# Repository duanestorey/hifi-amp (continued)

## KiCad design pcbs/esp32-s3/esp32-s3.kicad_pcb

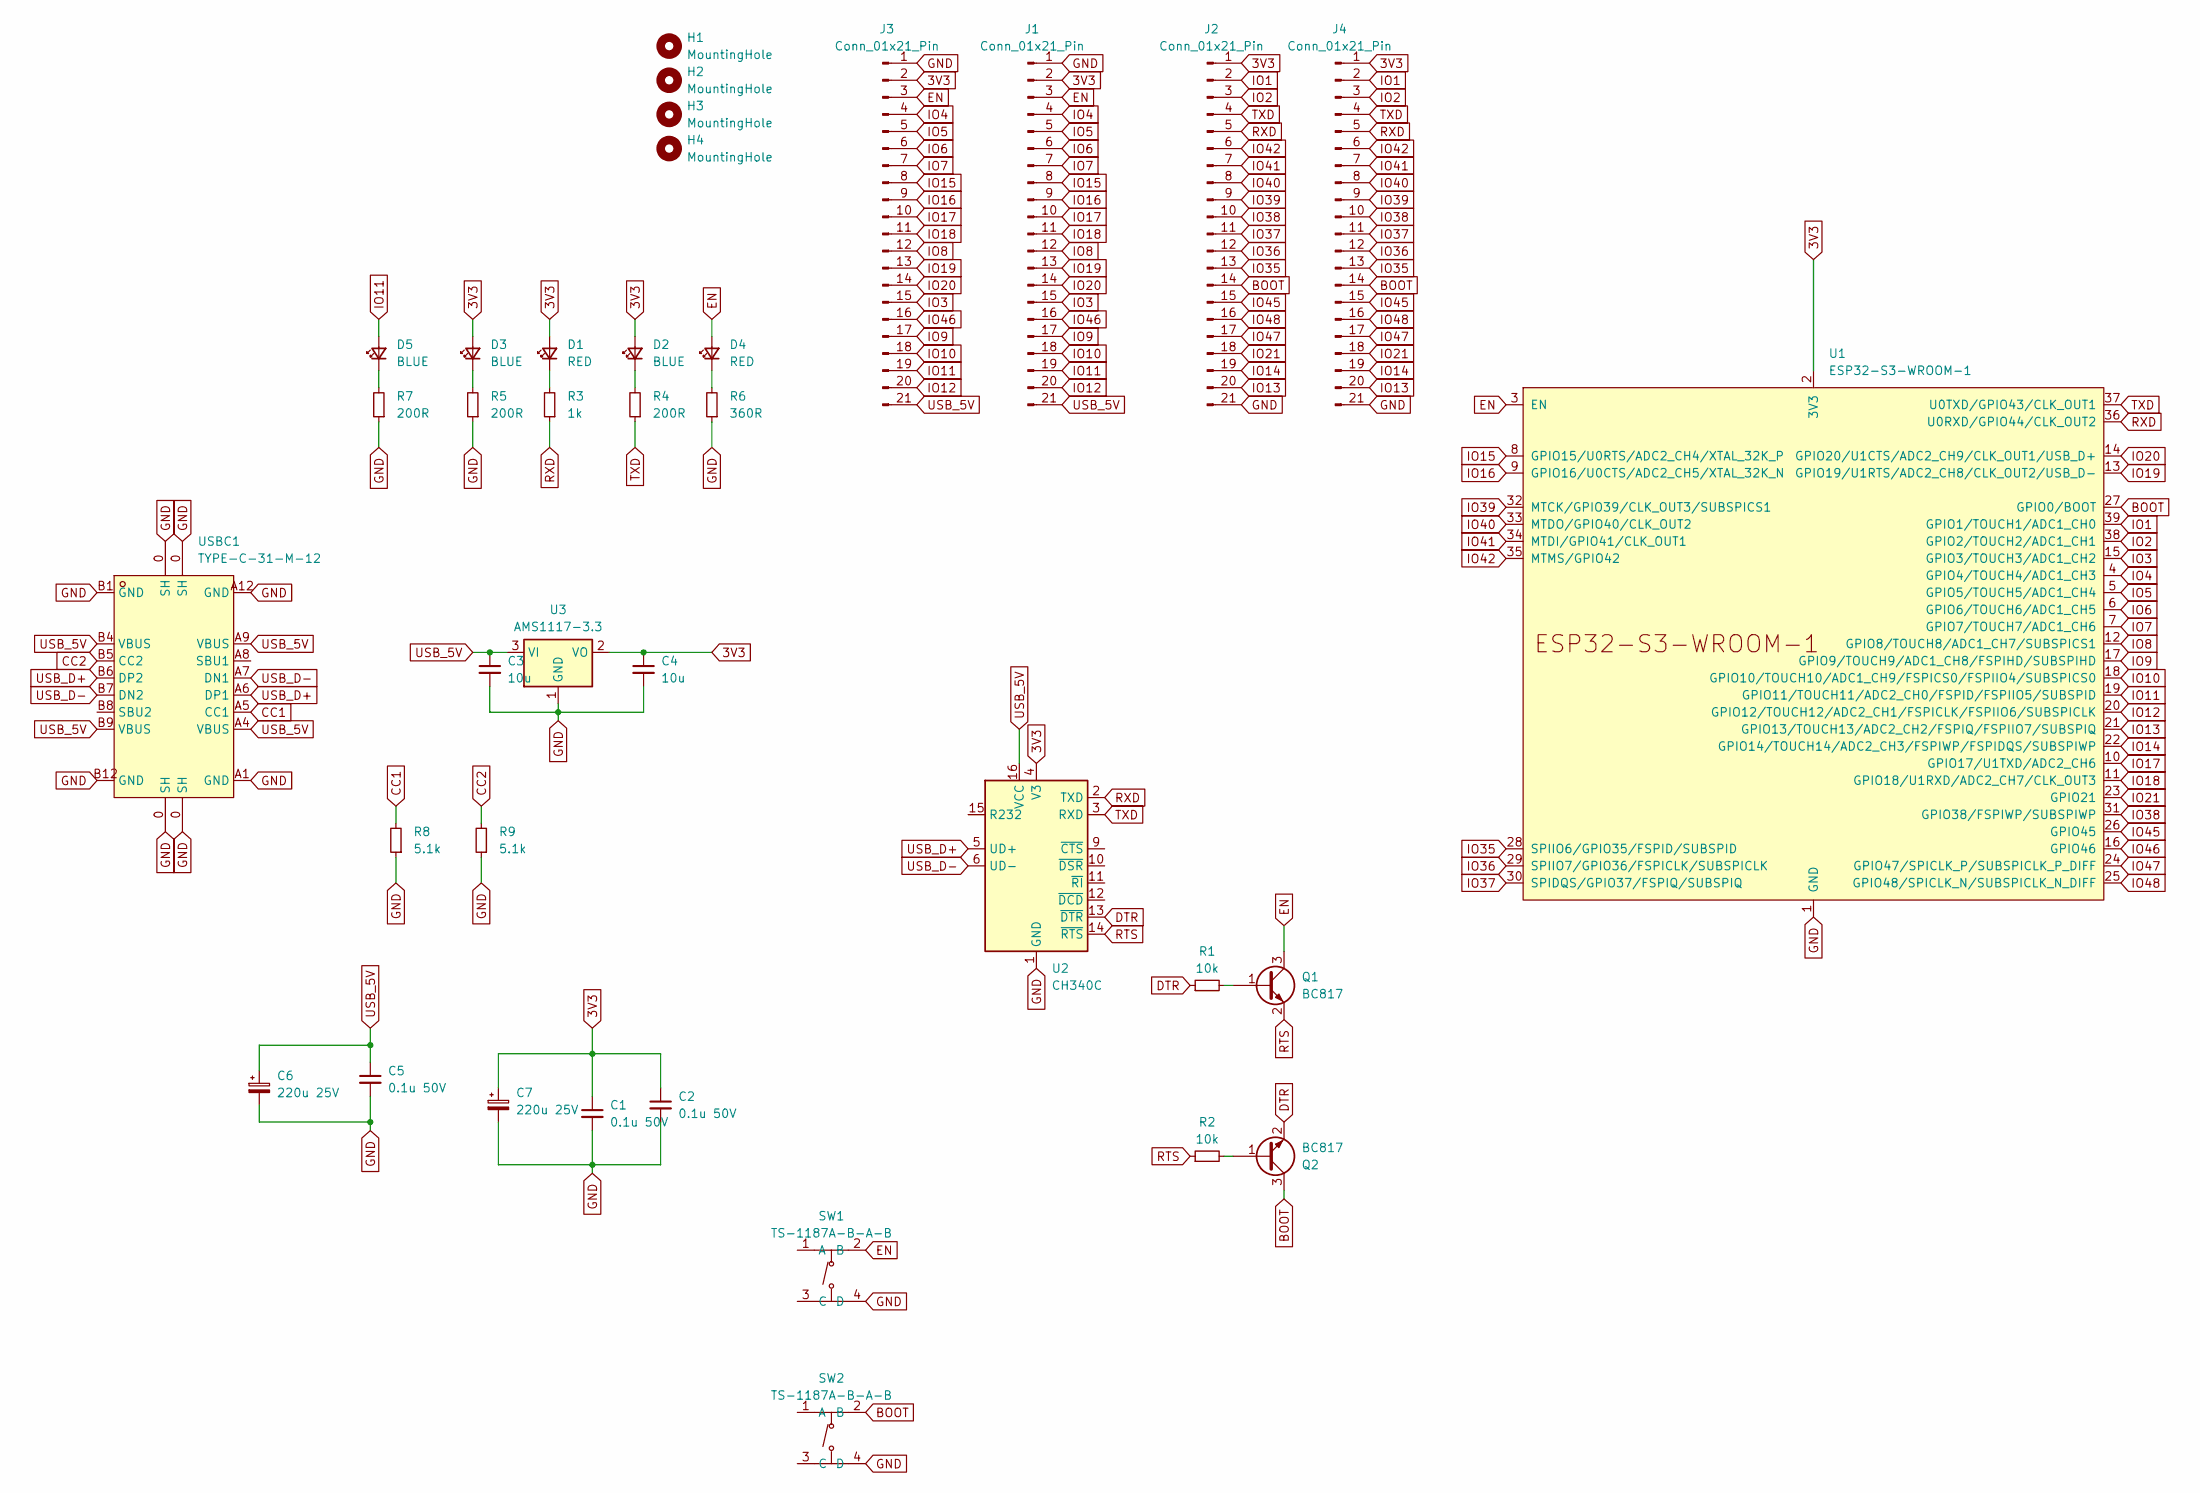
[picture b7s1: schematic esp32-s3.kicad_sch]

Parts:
C1, C2, C5: 0.1u 50V; C_0805_2012Metric; LCSC C38141
C3, C4: 10u; C_1206_3216Metric; LCSC C14860
C6, C7: 220u 25V; CP_Elec_6.3x7.7; LCSC C2918361
D1, D4: RED; LED_0603_1608Metric
D2, D3, D5: BLUE; LED_0603_1608Metric; LCSC C19171394
H1, H2, H3, H4: MountingHole; MountingHole_3.2mm_M3_DIN965_Pad_TopBottom
J1, J2: Conn_01x21_Pin; PinHeader_1x21_P2.54mm_Vertical; LCSC C41375940
J3, J4: Conn_01x21_Pin; PinSocket_1x21_P2.54mm_Vertical; LCSC C41376160
Q1, Q2: BC817; SOT-23; LCSC C52801
R1, R2: 10k; R_0603_1608Metric; LCSC C2930027
R3: 1k; R_0603_1608Metric
R4, R5: 200R; R_0603_1608Metric; LCSC C8218
R6: 360R; R_0603_1608Metric; LCSC C25194
R7: 200R; R_0603_1608Metric
R8, R9: 5.1k; R_0603_1608Metric; LCSC C23186
SW1, SW2: TS-1187A-B-A-B; SW-SMD_4P-L5.1-W5.1-P3.70-LS6.5-TL_H1.5; LCSC Part C318884
U1: ESP32-S3-WROOM-1; LCSC C2913203
U2: CH340C; SOIC-16_3.9x9.9mm_P1.27mm
U3: AMS1117-3.3; SOT-223-3_TabPin2; LCSC C5250992
USBC1: TYPE-C-31-M-12; USB-C_SMD-TYPE-C-31-M-12; LCSC Part C165948

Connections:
3V3: C1.1, C2.1, C4.1, C7.1, D1.2 (A), D2.2 (A), D3.2 (A), J1.2, J2.1, J3.2, J4.1, U1.2 (3V3), U2.4 (V3), U3.2 (VO)
BOOT: J2.14, J4.14, Q2.3 (C), SW2.2 (B), U1.27 (GPIO0/BOOT)
CC1: R8.2, USBC1.A5 (CC1)
CC2: R9.2, USBC1.B5 (CC2)
DTR: Q2.2 (E), R1.1, U2.13 (~DTR)
EN: D4.2 (A), J1.3, J3.3, Q1.3 (C), SW1.2 (B), U1.3 (EN)
GND: C1.2, C2.2, C3.2, C4.2, C5.2, C6.2, C7.2, J1.1, J2.21, J3.1, J4.21, R5.1, R6.1, R7.1, R8.1, R9.1, SW1.4 (D), SW2.4 (D), U1.1 (GND), U1.40 (GND), U1.41 (GND), U2.1 (GND), U3.1 (GND), USBC1.0 (SH), USBC1.A1 (GND), USBC1.A12 (GND), USBC1.B1 (GND), USBC1.B12 (GND)
IO1: J2.2, J4.2, U1.39 (GPIO1/TOUCH1/ADC1_CH0)
IO2: J2.3, J4.3, U1.38 (GPIO2/TOUCH2/ADC1_CH1)
IO3: J1.15, J3.15, U1.15 (GPIO3/TOUCH3/ADC1_CH2)
IO4: J1.4, J3.4, U1.4 (GPIO4/TOUCH4/ADC1_CH3)
IO5: J1.5, J3.5, U1.5 (GPIO5/TOUCH5/ADC1_CH4)
IO6: J1.6, J3.6, U1.6 (GPIO6/TOUCH6/ADC1_CH5)
IO7: J1.7, J3.7, U1.7 (GPIO7/TOUCH7/ADC1_CH6)
IO8: J1.12, J3.12, U1.12 (GPIO8/TOUCH8/ADC1_CH7/SUBSPICS1)
IO9: J1.17, J3.17, U1.17 (GPIO9/TOUCH9/ADC1_CH8/FSPIHD/SUBSPIHD)
IO10: J1.18, J3.18, U1.18 (GPIO10/TOUCH10/ADC1_CH9/FSPICS0/FSPIIO4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)
IO11: D5.2 (A), J1.19, J3.19, U1.19 (GPIO11/TOUCH11/ADC2_CH0/FSPID/FSPIIO5/S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)
IO12: J1.20, J3.20, U1.20 (GPIO12/TOUCH12/ADC2_CH1/FSPICLK/FSPIIO6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)
IO13: J2.20, J4.20, U1.21 (GPIO13/TOUCH13/ADC2_CH2/FSPIQ/FSPIIO7/S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)
IO14: J2.19, J4.19, U1.22 (GPIO14/TOUCH14/ADC2_CH3/FSPIWP/FSPIDQS/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)
IO15: J1.8, J3.8, U1.8 (GPIO15/U0RTS/ADC2_CH4/XTAL_32K_P)
IO16: J1.9, J3.9, U1.9 (GPIO16/U0CTS/ADC2_CH5/XTAL_32K_N)
IO17: J1.10, J3.10, U1.10 (GPIO17/U1TXD/ADC2_CH6)
IO18: J1.11, J3.11, U1.11 (GPIO18/U1RXD/ADC2_CH7/CLK_OUT3)
IO19: J1.13, J3.13, U1.13 (GPIO19/U1RTS/ADC2_CH8/CLK_OUT2/USB_D-)
IO20: J1.14, J3.14, U1.14 (GPIO20/U1CTS/ADC2_CH9/CLK_OUT1/USB_D+)
IO21: J2.18, J4.18, U1.23 (GPIO21)
IO35: J2.13, J4.13, U1.28 (SPIIO6/GPIO35/FSPID/SUBSPID)
IO36: J2.12, J4.12, U1.29 (SPIIO7/GPIO36/FSPICLK/SUBSPICLK)
IO37: J2.11, J4.11, U1.30 (SPIDQS/GPIO37/FSPIQ/SUBSPIQ)
IO38: J2.10, J4.10, U1.31 (GPIO38/FSPIWP/SUBSPIWP)
IO39: J2.9, J4.9, U1.32 (MTCK/GPIO39/CLK_OUT3/SUBSPICS1)
IO40: J2.8, J4.8, U1.33 (MTDO/GPIO40/CLK_OUT2)
IO41: J2.7, J4.7, U1.34 (MTDI/GPIO41/CLK_OUT1)
IO42: J2.6, J4.6, U1.35 (MTMS/GPIO42)
IO45: J2.15, J4.15, U1.26 (GPIO45)
IO46: J1.16, J3.16, U1.16 (GPIO46)
IO47: J2.17, J4.17, U1.24 (GPIO47/SPICLK_P/SUBSPICLK_P_DIFF)
IO48: J2.16, J4.16, U1.25 (GPIO48/SPICLK_N/SUBSPICLK_N_DIFF)
unnamed: D1.1 (K), R3.2
unnamed: D2.1 (K), R4.2
unnamed: D3.1 (K), R5.2
unnamed: D4.1 (K), R6.2
unnamed: D5.1 (K), R7.2
unnamed: Q1.1 (B), R1.2
unnamed: Q2.1 (B), R2.2
RTS: Q1.2 (E), R2.1, U2.14 (~RTS)
RXD: J2.5, J4.5, R3.1, U1.36 (U0RXD/GPIO44/CLK_OUT2), U2.2 (TXD)
TXD: J2.4, J4.4, R4.1, U1.37 (U0TXD/GPIO43/CLK_OUT1), U2.3 (RXD)
USB_5V: C3.1, C5.1, C6.1, J1.21, J3.21, U2.16 (VCC), U3.3 (VI), USBC1.A4 (VBUS), USBC1.A9 (VBUS), USBC1.B4 (VBUS), USBC1.B9 (VBUS)
USB_D+: U2.5 (UD+), USBC1.A6 (DP1), USBC1.B6 (DP2)
USB_D-: U2.6 (UD-), USBC1.A7 (DN1), USBC1.B7 (DN2)

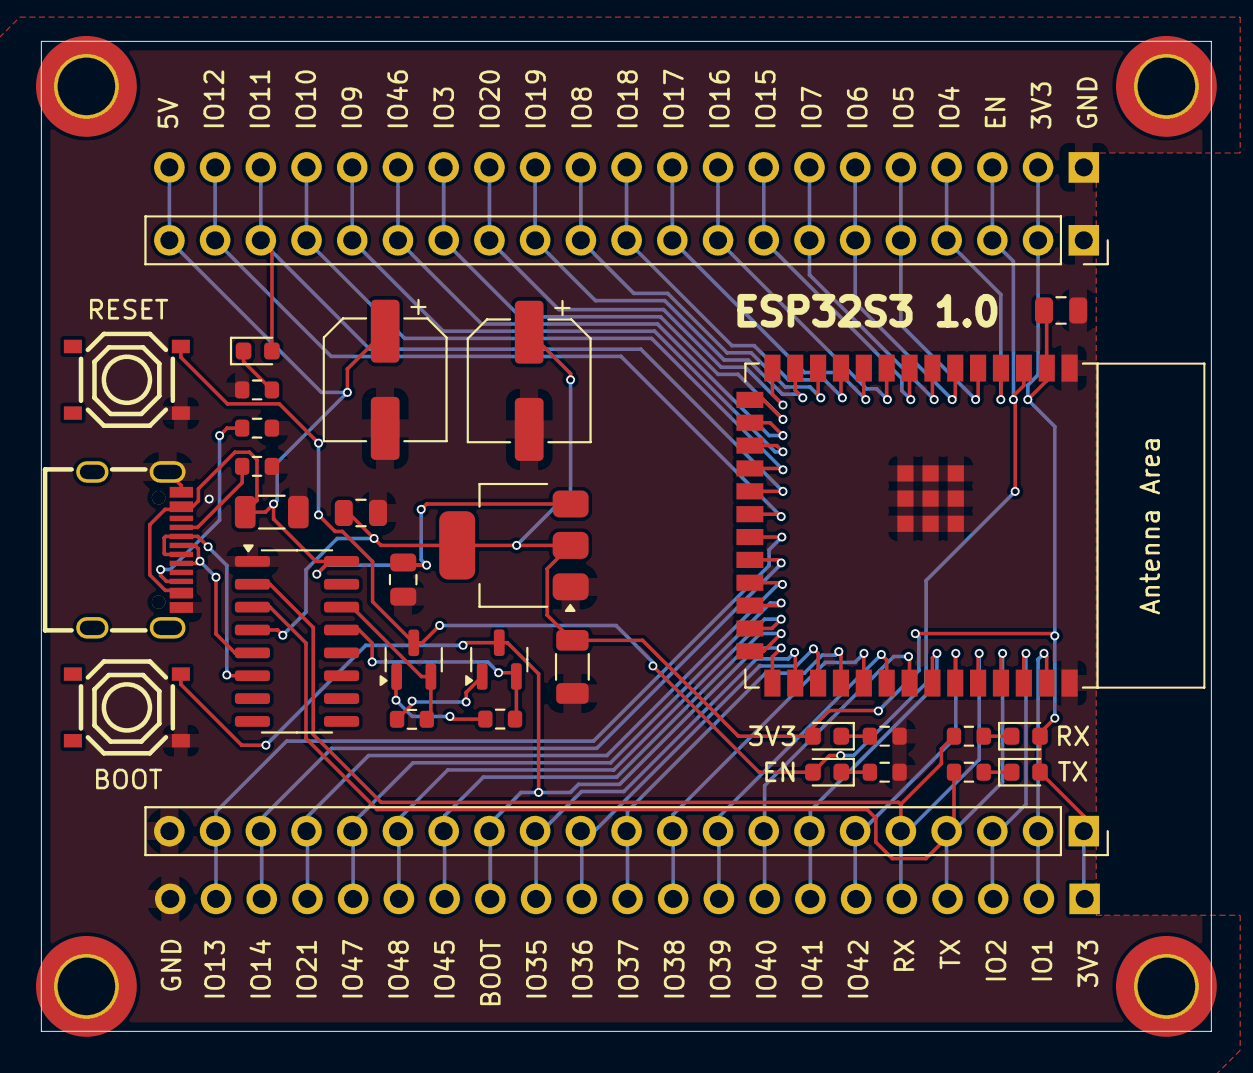
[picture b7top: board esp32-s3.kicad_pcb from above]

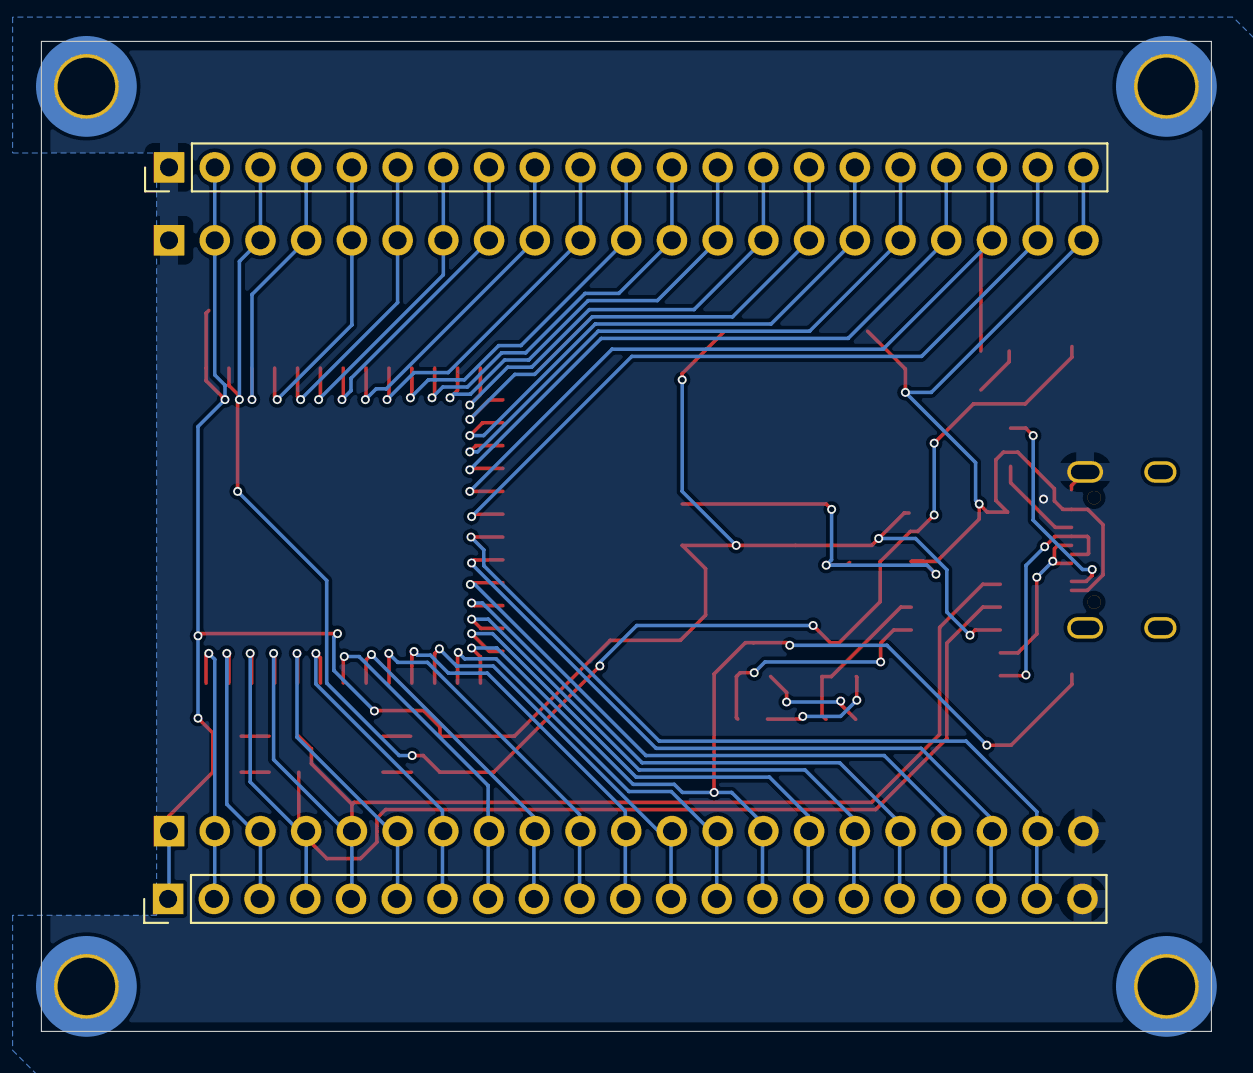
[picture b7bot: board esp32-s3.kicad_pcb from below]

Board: 2 copper layers, 65.0 x 55.0 mm, 37 parts (2 on the bottom side), 53 nets.
